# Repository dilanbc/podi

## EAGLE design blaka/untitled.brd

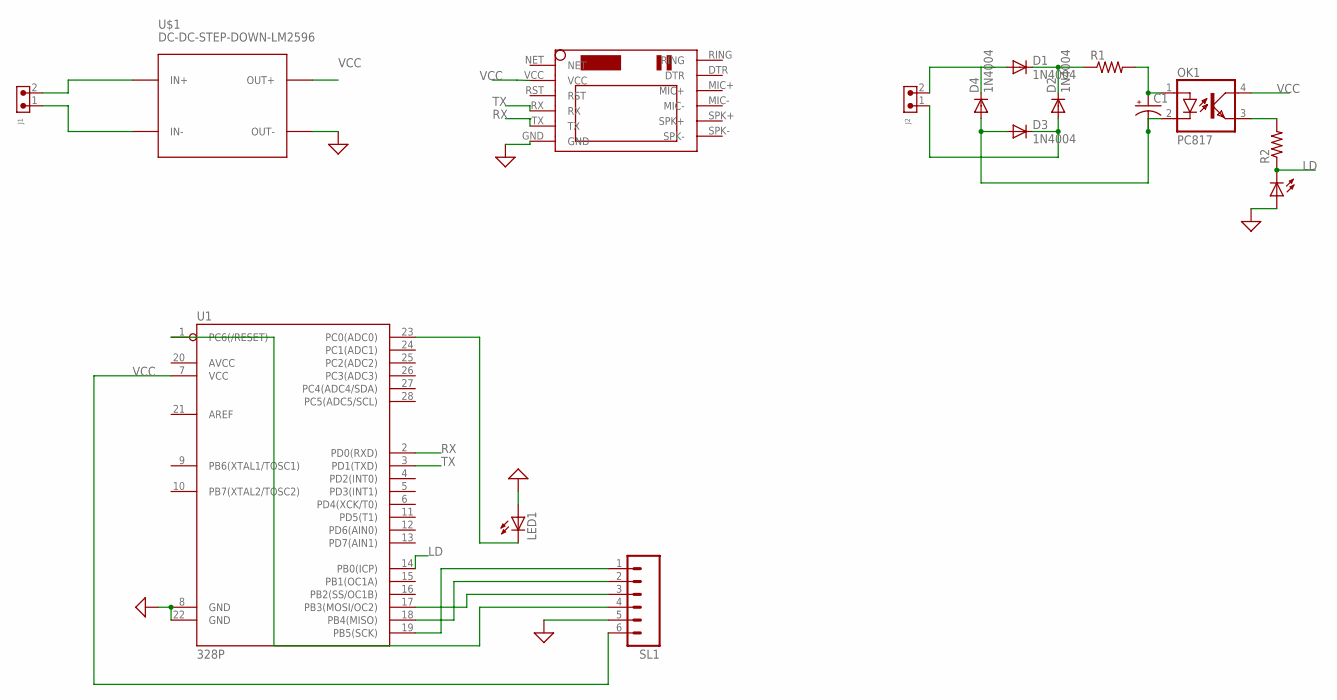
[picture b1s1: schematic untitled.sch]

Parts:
C1: CPOL-USE2.5-5; E2,5-5
D1, D2, D3, D4: 1N4004; DO41-10
J1, J2: 691305530002
LED1, LED2: LED5MM
OK1: PC817; DIL04
R1, R2: R-US_0207/10; 0207/10
SL1: M06; 06P
U1: 328P; DIP28
U$1: DC-DC-STEP-DOWN-LM2596
U$2: SIM800LMODULE

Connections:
GND: LED1.A, LED2.A, SL1.5, U1.8 (GND), U1.22 (GND), U$1.OUT-, U$2.GND
LD: LED2.K (C), OK1.3 (EMIT), R2.1, R2.2, U1.14 (PB0(ICP))
unnamed: J1.2, U$1.IN+
unnamed: J1.1, U$1.IN-
unnamed: D1.A, D4.C, J2.2
unnamed: SL1.1, U1.19 (PB5(SCK))
unnamed: SL1.2, U1.18 (PB4(MISO))
unnamed: SL1.3, U1.17 (PB3(MOSI/OC2))
unnamed: SL1.4, U1.1 (PC6(/RESET))
unnamed: LED1.K (C), U1.23 (PC0(ADC0))
unnamed: D1.C, D2.C, R1.1
unnamed: D2.A, D3.C, J2.1
unnamed: C1.-, D3.A, D4.A, OK1.2 (C)
unnamed: C1.+, OK1.1 (A), R1.2
RX: U1.2 (PD0(RXD)), U$2.TX
TX: U1.3 (PD1(TXD)), U$2.RX
VCC: OK1.4 (COL), SL1.6, U1.7 (VCC), U$1.OUT+, U$2.VCC

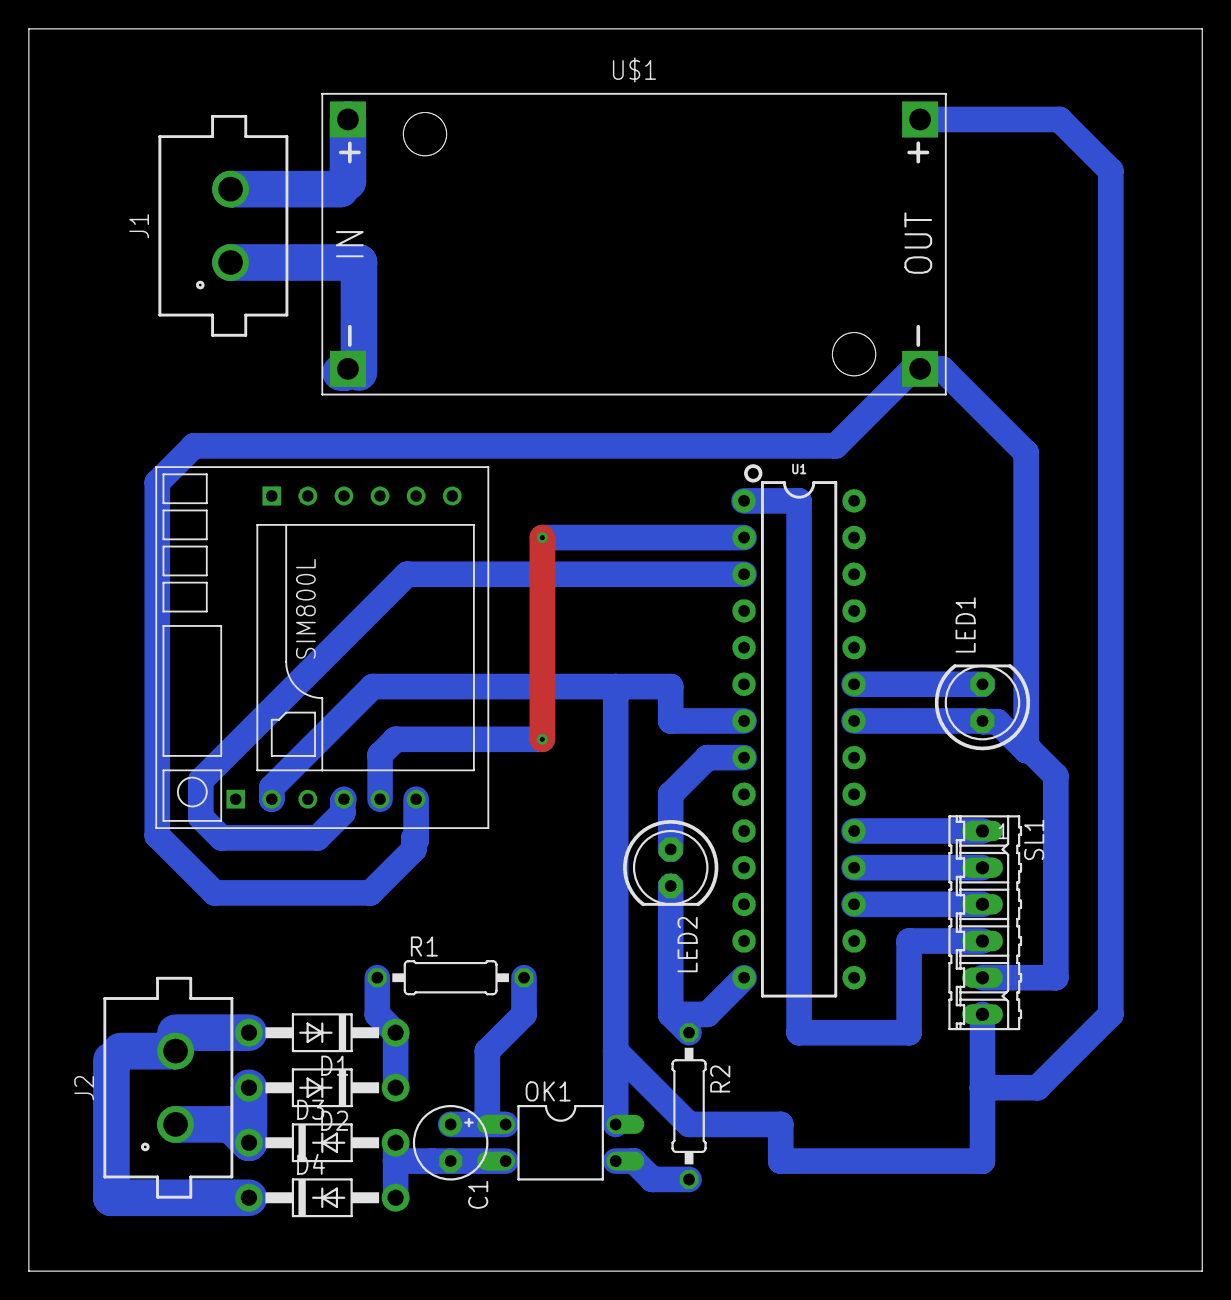
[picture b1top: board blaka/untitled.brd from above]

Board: 2 copper layers, 81.3 x 86.0 mm, 16 parts (0 on the bottom side), 17 nets.

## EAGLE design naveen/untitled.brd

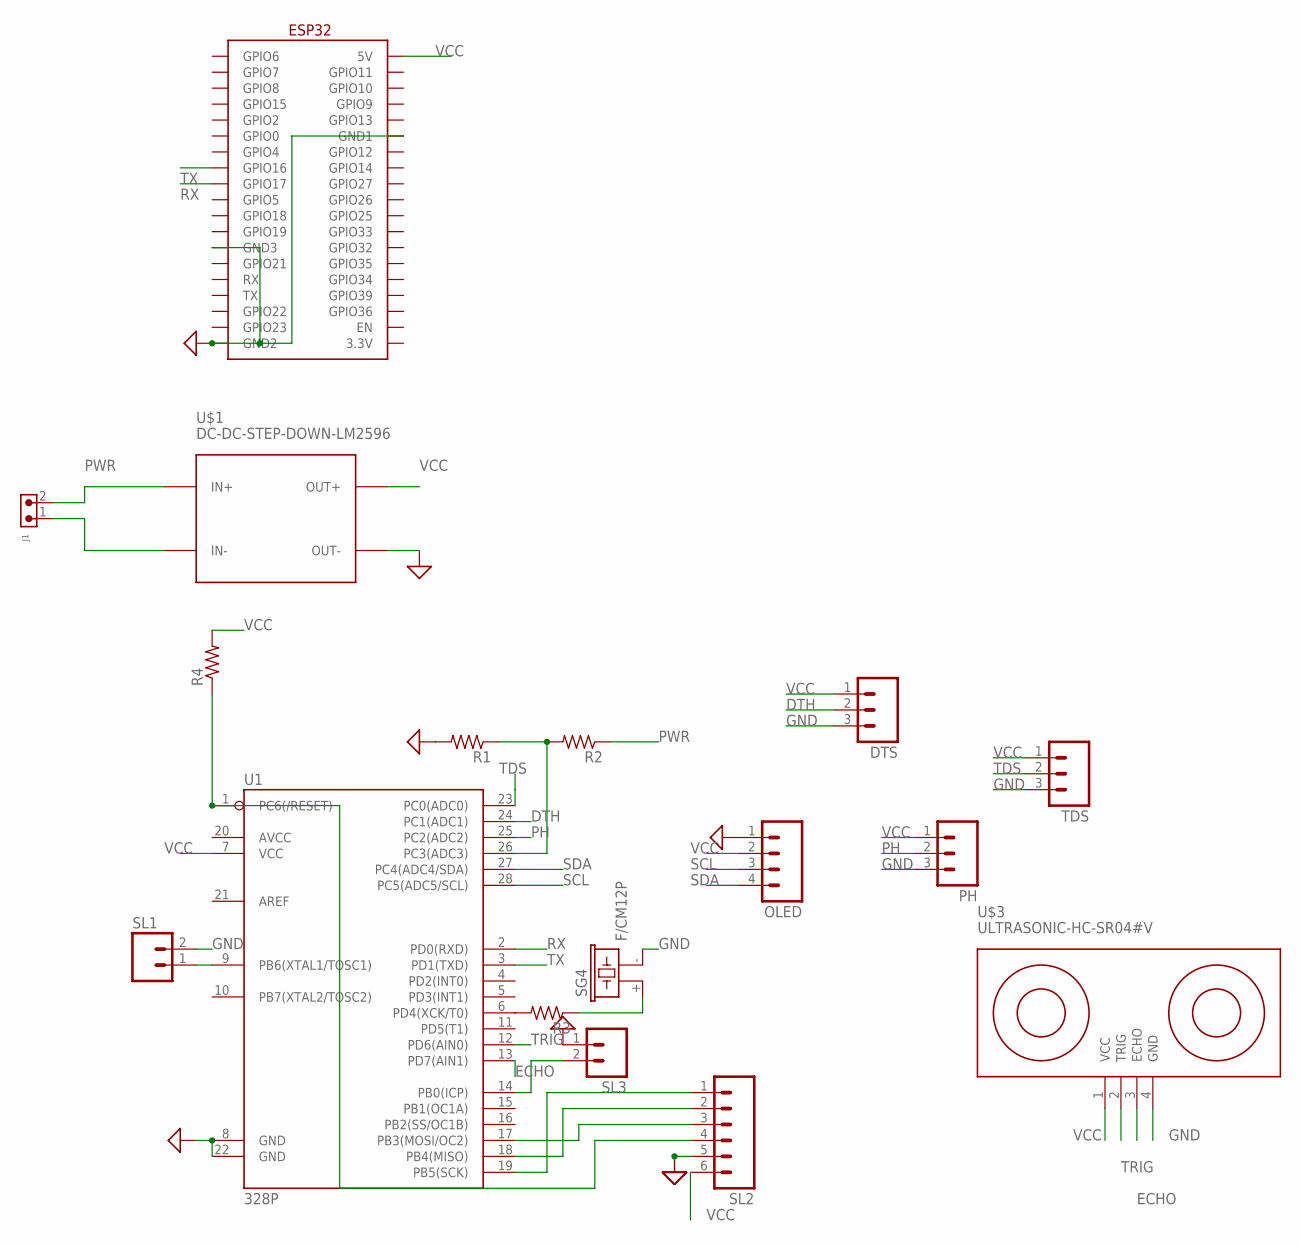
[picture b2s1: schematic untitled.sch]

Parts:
DTS: M03; 03P
J1: 691305530002
OLED: M04; 04P
PH: M03; 03P
R1, R2, R4: R-US_0207/10; 0207/10
R3: R-US_0204/2V; 0204V
SG4: F/CM12P
SL1, SL3: M02; 02P
SL2: M06; 06P
TDS: M03; 03P
U1: 328P; DIP28
U$1: DC-DC-STEP-DOWN-LM2596
U$2: ESP32
U$3: ULTRASONIC-HC-SR04#V

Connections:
DTH: DTS.2, U1.24 (PC1(ADC1))
ECHO: U1.13 (PD7(AIN1)), U$3.3 (ECHO)
GND: DTS.3, OLED.1, PH.3, R1.2, SG4.- (2), SL1.2, SL2.5, SL3.1, TDS.3, U1.8 (GND), U1.22 (GND), U$1.OUT-, U$2.GND1, U$2.GND2, U$2.GND3, U$3.4 (GND)
unnamed: R1.1, R2.2, U1.26 (PC3(ADC3))
unnamed: J1.1, U$1.IN-
unnamed: SL3.2, U1.14 (PB0(ICP))
unnamed: SL2.1, U1.19 (PB5(SCK))
unnamed: SL2.2, U1.18 (PB4(MISO))
unnamed: SL2.3, U1.17 (PB3(MOSI/OC2))
unnamed: R4.1, SL2.4, U1.1 (PC6(/RESET))
unnamed: SL1.1, U1.9 (PB6(XTAL1/TOSC1))
unnamed: R3.2, U1.6 (PD4(XCK/T0))
unnamed: R3.1, SG4.+ (1)
PH: PH.2, U1.25 (PC2(ADC2))
PWR: J1.2, R2.1, U$1.IN+
RX: U1.2 (PD0(RXD)), U$2.GPIO17
SCL: OLED.3, U1.28 (PC5(ADC5/SCL))
SDA: OLED.4, U1.27 (PC4(ADC4/SDA))
TDS: TDS.2, U1.23 (PC0(ADC0))
TRIG: U1.12 (PD6(AIN0)), U$3.2 (TRIG)
TX: U1.3 (PD1(TXD)), U$2.GPIO16
VCC: DTS.1, OLED.2, PH.1, R4.2, SL2.6, TDS.1, U1.7 (VCC), U$1.OUT+, U$2.5V, U$3.1 (VCC)

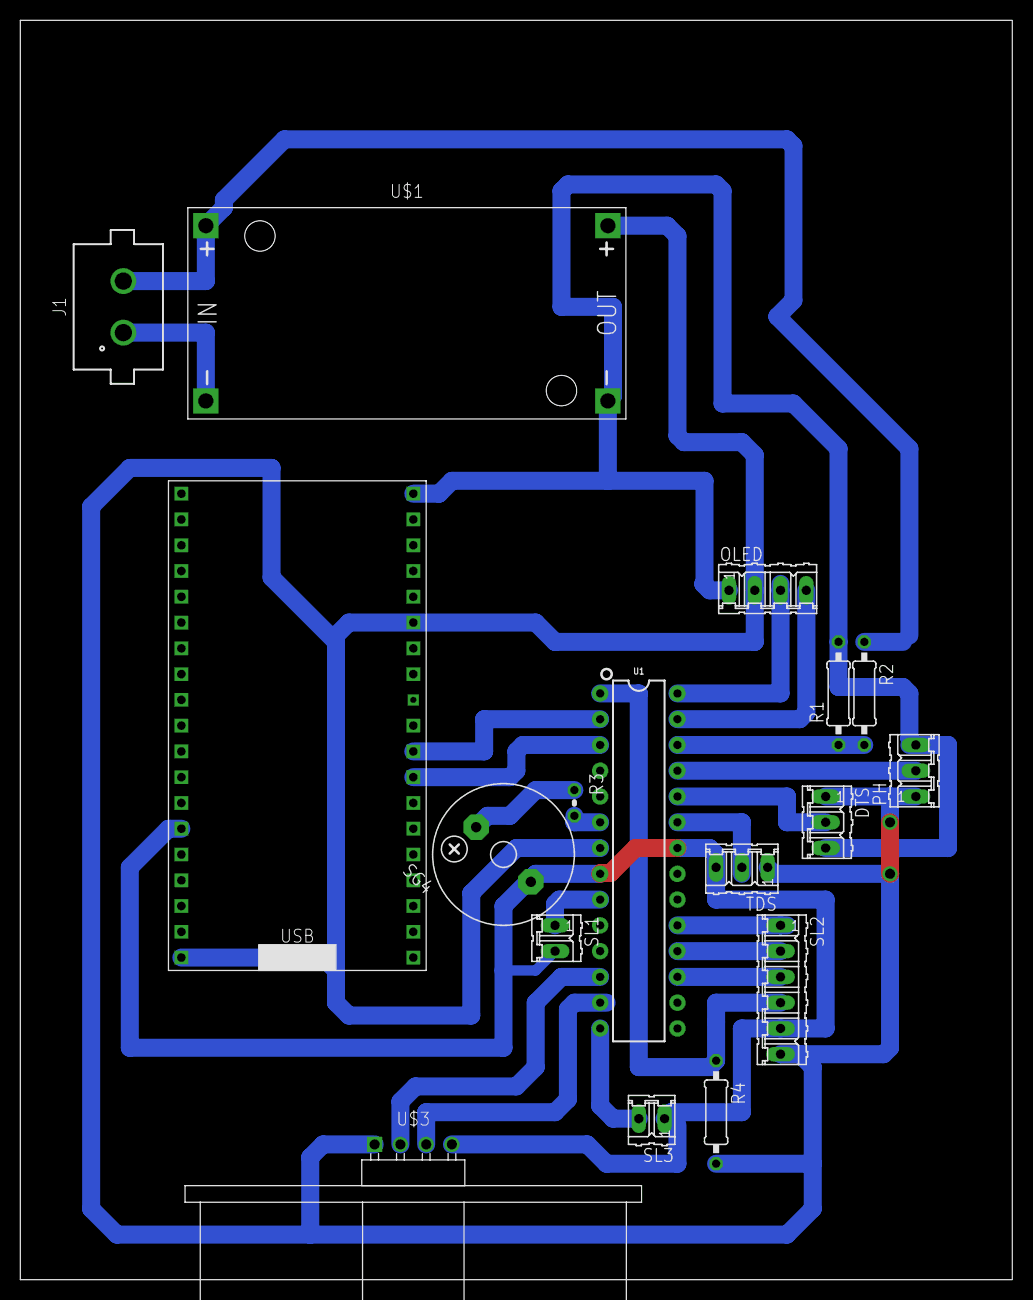
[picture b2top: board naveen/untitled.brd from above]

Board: 2 copper layers, 97.8 x 124.1 mm, 17 parts (0 on the bottom side), 22 nets.

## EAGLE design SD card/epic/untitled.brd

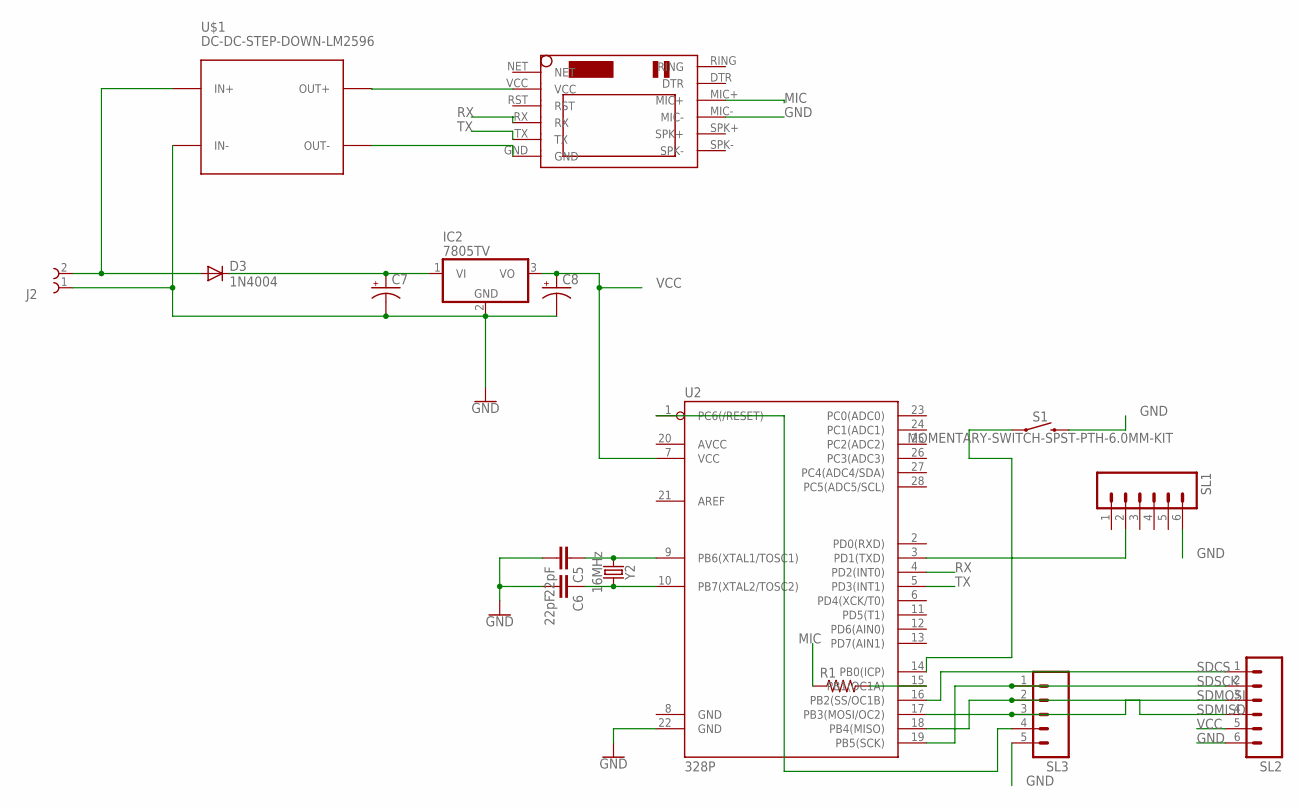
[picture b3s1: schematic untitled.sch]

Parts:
C5, C6: 22pF; CAP-PTH-2.54
C7: CAPACITOR-PE5-8.5; E5-8,5
C8: CAPACITOR-PE5-5; E5-5
D3: 1N4004; DO41-10
IC2: 7805TV; TO220V
J2: 691201520002
R1: R-US_0207/10; 0207/10
S1: MOMENTARY-SWITCH-SPST-PTH-6.0MM-KIT; TACTILE_SWITCH_PTH_6.0MM_KIT
SL1, SL2: M06; 06P
SL3: M05; 05P
U2: 328P; DIP28
U$1: DC-DC-STEP-DOWN-LM2596
U$2: SIM800LMODULE
Y2: 16MHz; HC49US

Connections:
GND: C5.2, C6.2, C7.-, C8.-, IC2.2 (GND), J2.1, S1.3 (2), SL1.6, SL2.6, SL3.5, U2.22 (GND), U$1.IN-, U$2.MIC-
MIC: R1.1, U$2.MIC+
unnamed: U$1.OUT+, U$2.VCC
unnamed: U$1.OUT-, U$2.GND
unnamed: R1.2, U2.15 (PB1(OC1A))
unnamed: S1.1, U2.14 (PB0(ICP))
unnamed: SL3.4, U2.1 (PC6(/RESET))
unnamed: C5.1, U2.9 (PB6(XTAL1/TOSC1)), Y2.1
unnamed: C6.1, U2.10 (PB7(XTAL2/TOSC2)), Y2.2
unnamed: D3.A, J2.2, U$1.IN+
unnamed: C7.+, D3.C, IC2.1 (VI)
RX: U2.4 (PD2(INT0)), U$2.RX
SDCS: SL2.1, U2.16 (PB2(SS/OC1B))
SDMISO: SL2.4, SL3.2, U2.18 (PB4(MISO))
SDMOSI: SL2.3, SL3.3, U2.17 (PB3(MOSI/OC2))
SDSCK: SL2.2, SL3.1, U2.19 (PB5(SCK))
TX: U2.5 (PD3(INT1)), U$2.TX
TX1: SL1.2, U2.3 (PD1(TXD))
VCC: C8.+, IC2.3 (VO), SL2.5, U2.7 (VCC)

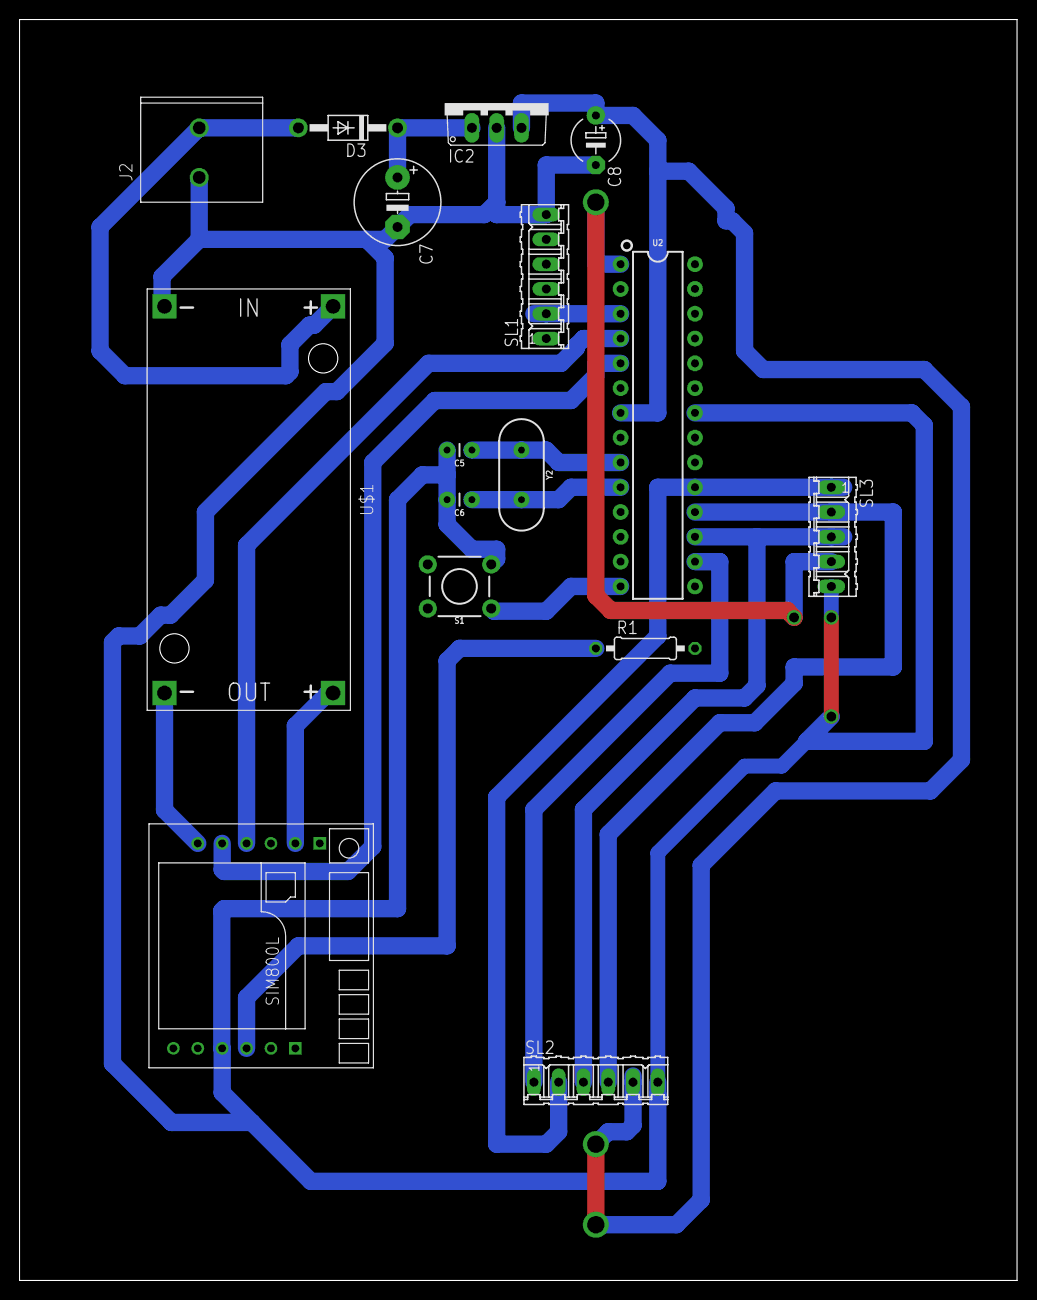
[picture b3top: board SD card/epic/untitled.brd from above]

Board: 2 copper layers, 102.2 x 129.2 mm, 16 parts (0 on the bottom side), 19 nets.

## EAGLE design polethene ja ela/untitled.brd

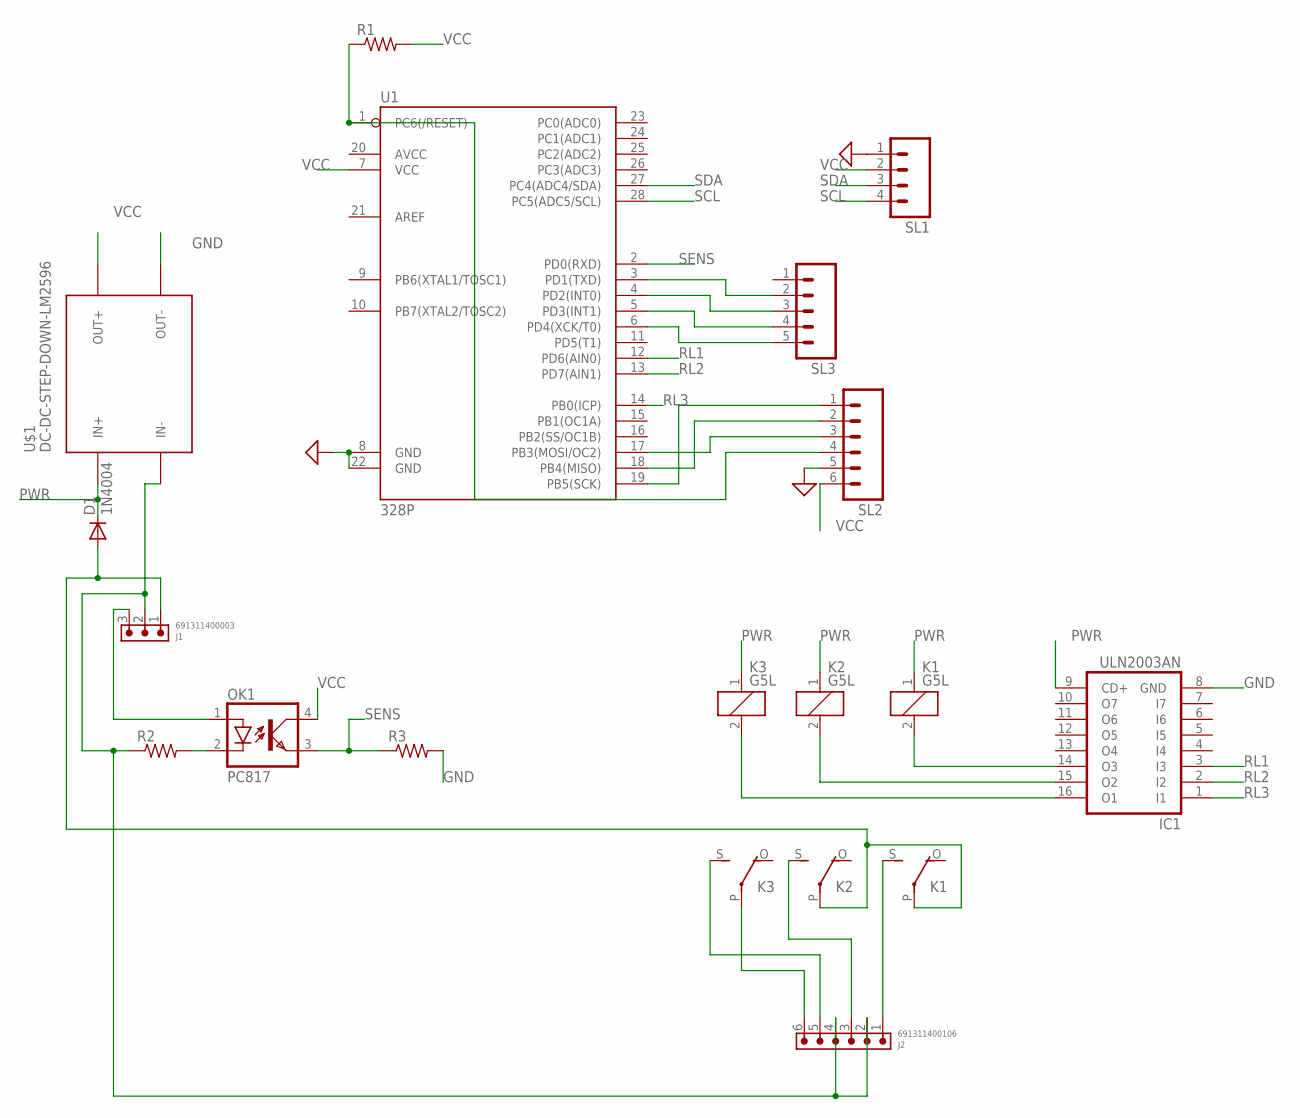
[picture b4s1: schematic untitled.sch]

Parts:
D1: 1N4004; DO41-10
IC1: ULN2003AN; DIL16
J1: 691311400003
J2: 691311400106
K1, K2, K3: G5L; G5LE
OK1: PC817; DIL04
R1, R2, R3: R-US_0207/7; 0207/7
SL1: M04; 04P
SL2: M06; 06P
SL3: M05; 05P
U1: 328P; DIP28
U$1: DC-DC-STEP-DOWN-LM2596

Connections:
GND: IC1.8 (GND), R3.2, SL1.1, SL2.5, U1.8 (GND), U1.22 (GND), U$1.OUT-
unnamed: J2.1, K1.S
unnamed: D1.A, J1.1, K1.P, K2.P
unnamed: J1.3, OK1.1 (A)
unnamed: SL2.1, U1.19 (PB5(SCK))
unnamed: SL2.2, U1.18 (PB4(MISO))
unnamed: SL2.3, U1.17 (PB3(MOSI/OC2))
unnamed: R1.1, SL2.4, U1.1 (PC6(/RESET))
unnamed: OK1.2 (C), R2.2
unnamed: J2.3, K2.S
unnamed: SL3.2, U1.3 (PD1(TXD))
unnamed: J2.5, K3.S
unnamed: J2.6, K3.P
unnamed: IC1.14 (O3), K1.2
unnamed: IC1.15 (O2), K2.2
unnamed: IC1.16 (O1), K3.2
unnamed: J1.2, J2.2, J2.4, R2.1, U$1.IN-
unnamed: SL3.3, U1.4 (PD2(INT0))
unnamed: SL3.4, U1.5 (PD3(INT1))
unnamed: SL3.5, U1.6 (PD4(XCK/T0))
PWR: D1.C, IC1.9 (CD+), K1.1, K2.1, K3.1, U$1.IN+
RL1: IC1.3 (I3), U1.12 (PD6(AIN0))
RL2: IC1.2 (I2), U1.13 (PD7(AIN1))
RL3: IC1.1 (I1), U1.14 (PB0(ICP))
SCL: SL1.4, U1.28 (PC5(ADC5/SCL))
SDA: SL1.3, U1.27 (PC4(ADC4/SDA))
SENS: OK1.3 (EMIT), R3.1, U1.2 (PD0(RXD))
VCC: OK1.4 (COL), R1.2, SL1.2, SL2.6, U1.7 (VCC), U$1.OUT+

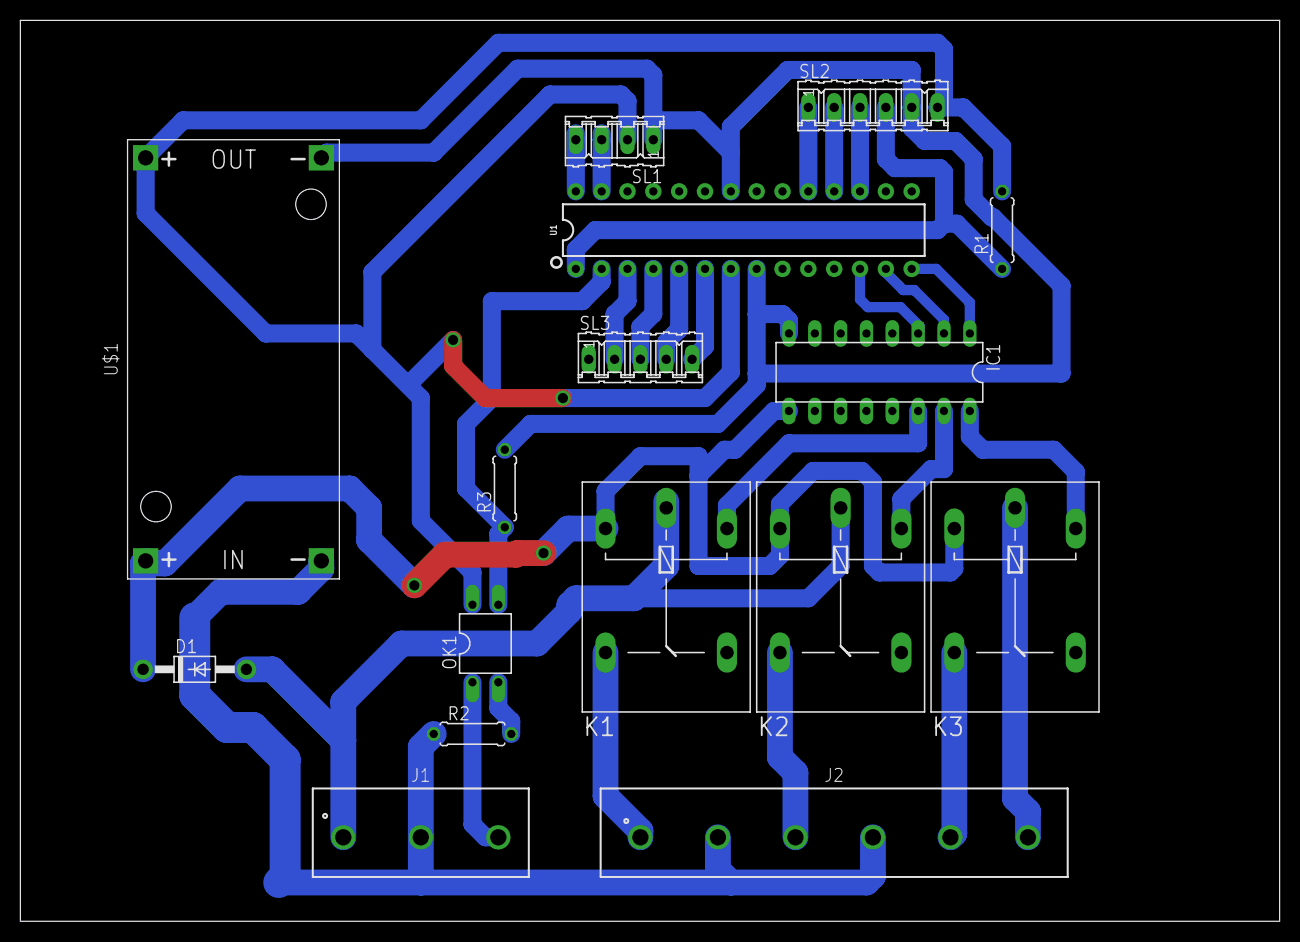
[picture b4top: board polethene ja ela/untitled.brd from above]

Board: 2 copper layers, 123.8 x 88.6 mm, 16 parts (0 on the bottom side), 28 nets.

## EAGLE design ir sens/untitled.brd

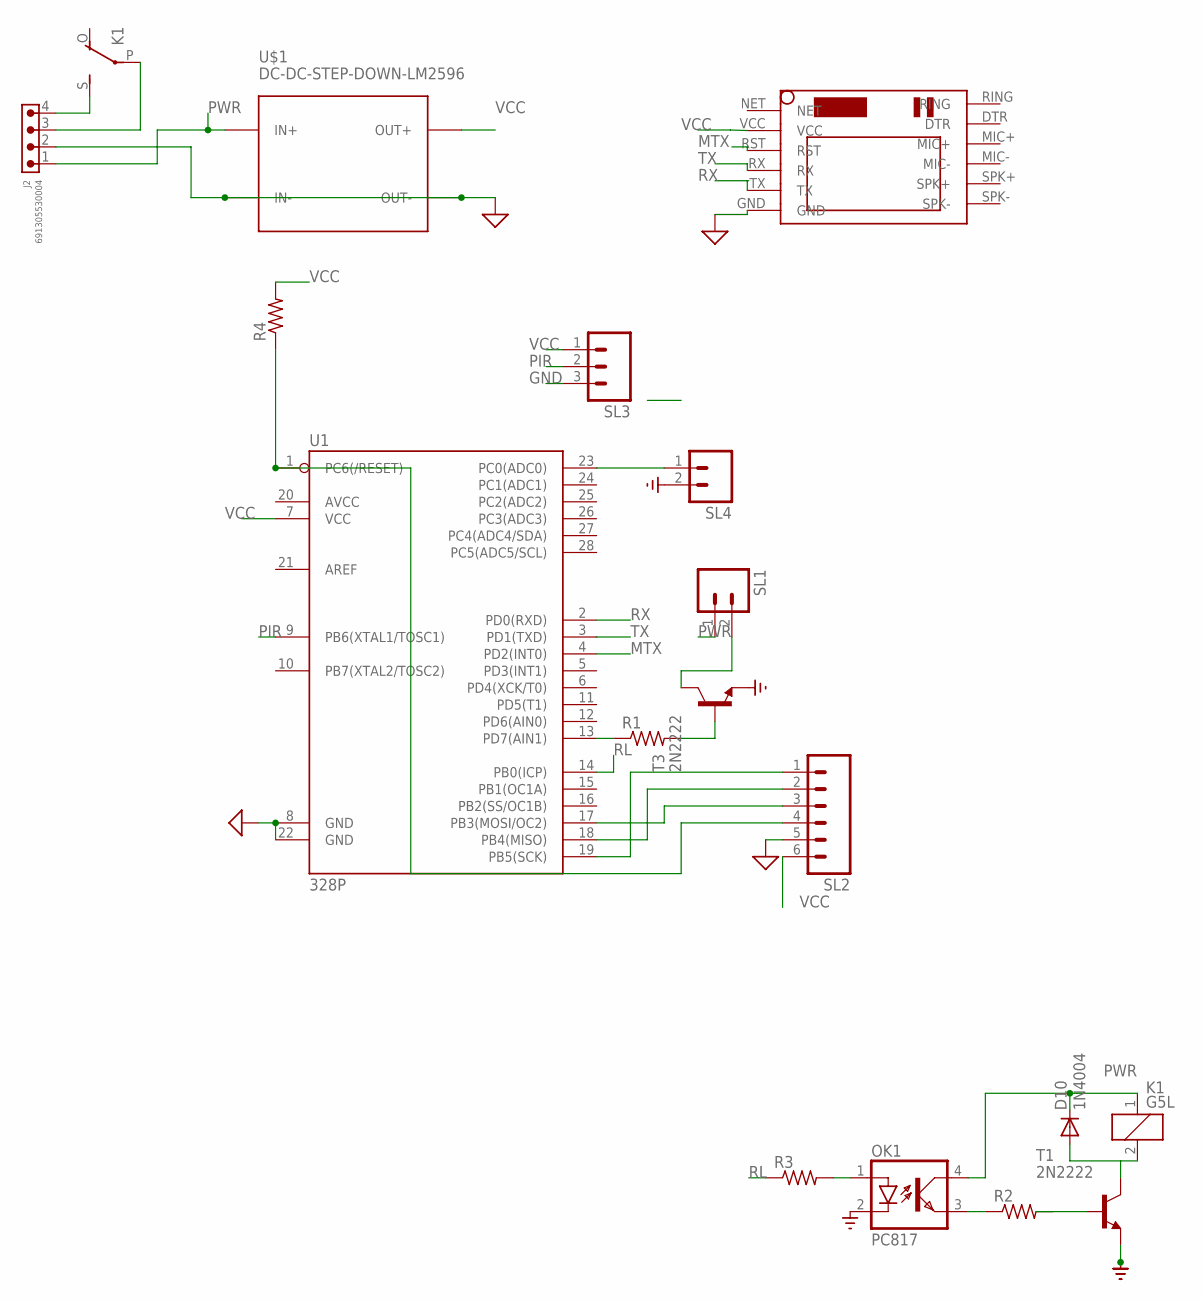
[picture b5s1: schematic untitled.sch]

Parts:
D10: 1N4004; DO41-10
J2: 691305530004
K1: G5L; G5LE
OK1: PC817; DIL04
R1, R2: R-US_0207/10; 0207/10
R3, R4: R-US_0207/15; 0207/15
SL1, SL4: M02; 02P
SL2: M06; 06P
SL3: M03; 03P
T1, T3: 2N2222; TO92-EBC-OVAL
U1: 328P; DIP28
U$1: DC-DC-STEP-DOWN-LM2596
U$2: SIM800LMODULE

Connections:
GND: J2.2, OK1.2 (C), SL2.5, SL3.3, SL4.2, T1.E, T3.E, U1.8 (GND), U1.22 (GND), U$1.IN-, U$1.OUT-, U$2.GND
MTX: U1.4 (PD2(INT0)), U$2.RST
unnamed: OK1.1 (A), R3.2
unnamed: SL1.2, T3.C
unnamed: J2.4, K1.S
unnamed: SL2.1, U1.19 (PB5(SCK))
unnamed: SL2.2, U1.18 (PB4(MISO))
unnamed: SL2.3, U1.17 (PB3(MOSI/OC2))
unnamed: R1.1, U1.13 (PD7(AIN1))
unnamed: J2.3, K1.P
unnamed: D10.A, K1.2, T1.C
unnamed: R1.2, T3.B
unnamed: SL4.1, U1.23 (PC0(ADC0))
unnamed: R2.2, T1.B
unnamed: OK1.3 (EMIT), R2.1
unnamed: R4.1, SL2.4, U1.1 (PC6(/RESET))
PIR: SL3.2, U1.9 (PB6(XTAL1/TOSC1))
PWR: D10.C, J2.1, K1.1, OK1.4 (COL), SL1.1, U$1.IN+
RL: R3.1, U1.14 (PB0(ICP))
RX: U1.2 (PD0(RXD)), U$2.TX
TX: U1.3 (PD1(TXD)), U$2.RX
VCC: R4.2, SL2.6, SL3.1, U1.7 (VCC), U$1.OUT+, U$2.VCC

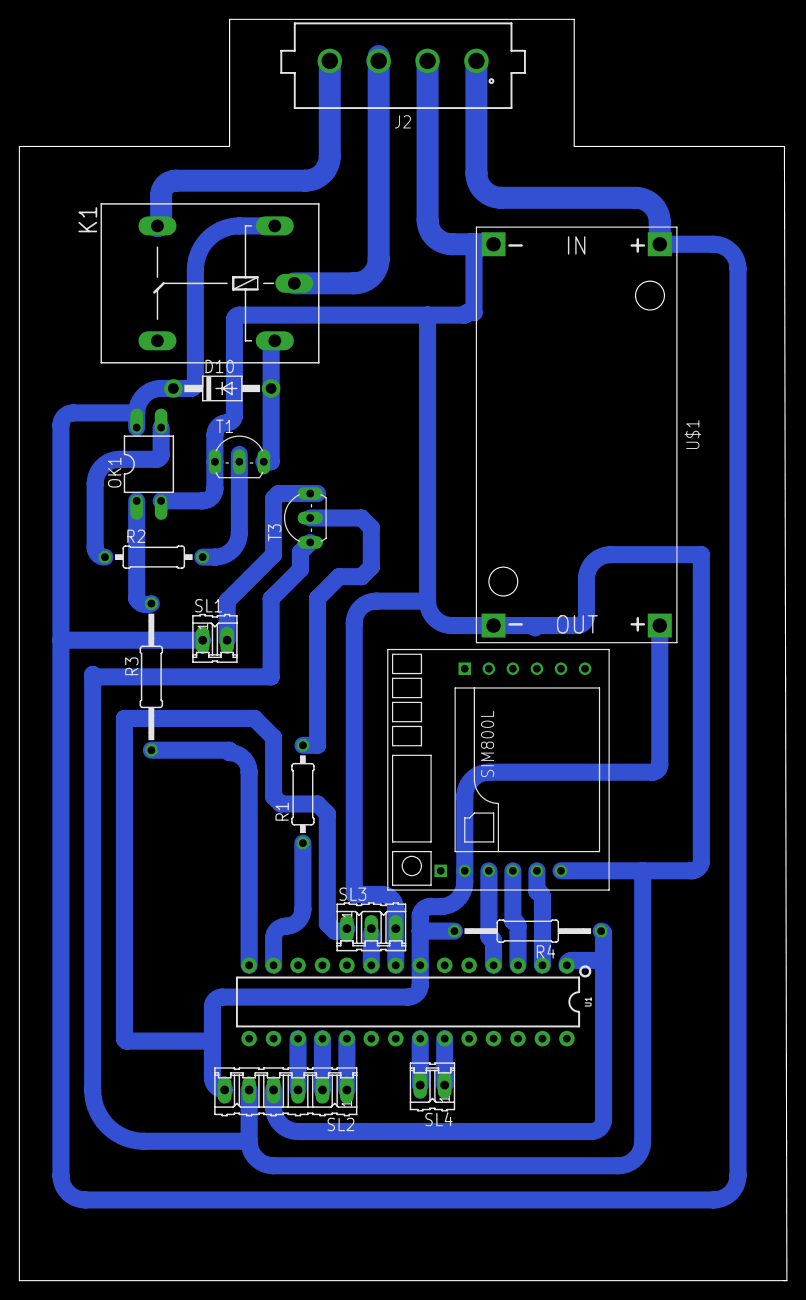
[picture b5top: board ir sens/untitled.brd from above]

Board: 2 copper layers, 79.8 x 131.1 mm, 17 parts (0 on the bottom side), 22 nets.

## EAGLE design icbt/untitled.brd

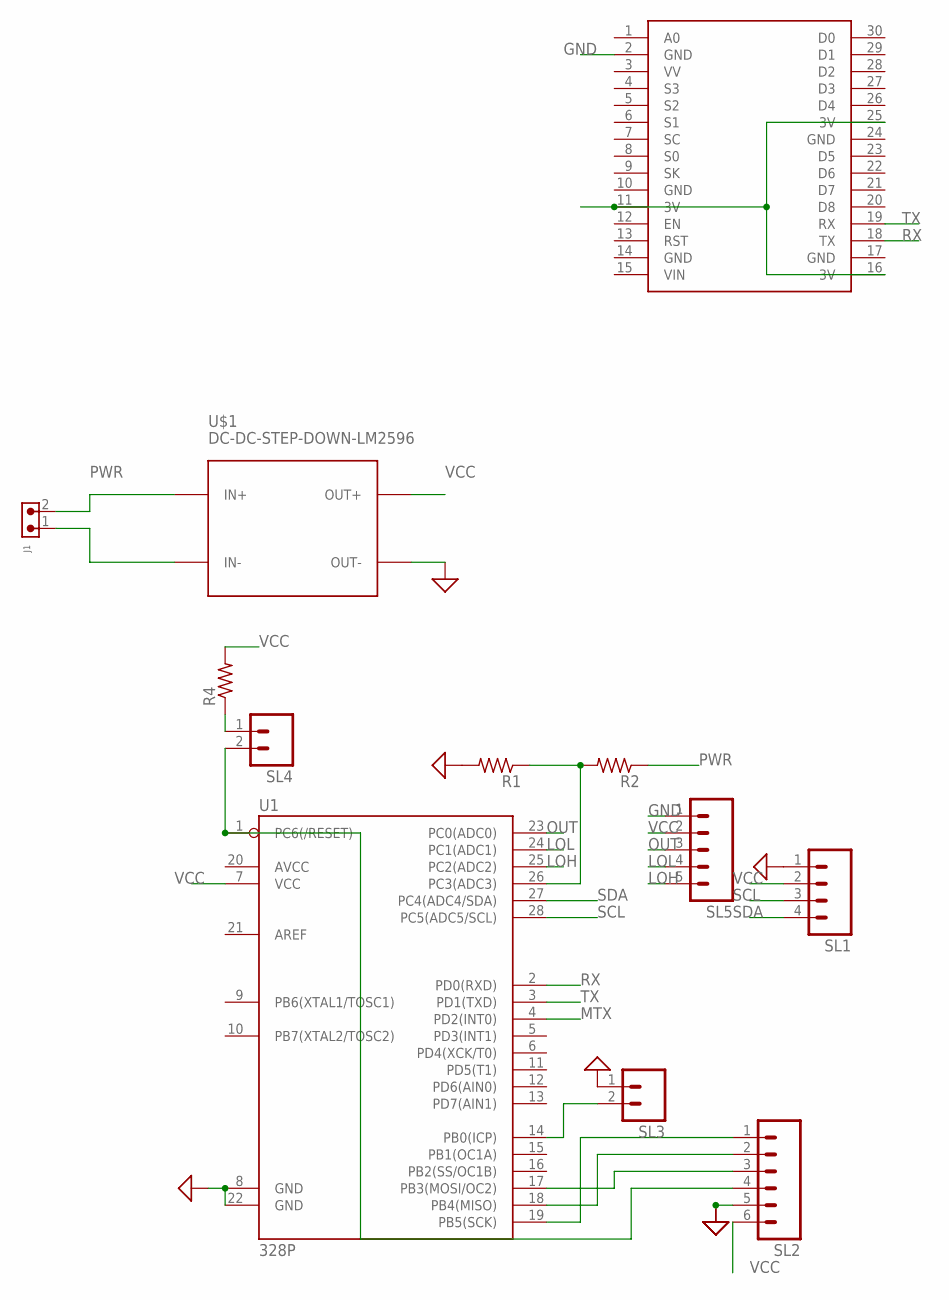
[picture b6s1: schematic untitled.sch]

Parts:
J1: 691305530002
R1, R2, R4: R-US_0207/10; 0207/10
SL1: M04; 04P
SL2: M06; 06P
SL3, SL4: M02; 02P
SL5: M05; 05P
U1: 328P; DIP28
U$1: DC-DC-STEP-DOWN-LM2596
U$3: NODEMCU

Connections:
GND: R1.2, SL1.1, SL2.5, SL3.1, SL5.1, U1.8 (GND), U1.22 (GND), U$1.OUT-, U$3.2 (GND), U$3.10 (GND), U$3.14 (GND), U$3.17 (GND), U$3.24 (GND)
LOH: SL5.5, U1.25 (PC2(ADC2))
LOL: SL5.4, U1.24 (PC1(ADC1))
MTX: U1.4 (PD2(INT0))
unnamed: R1.1, R2.2, U1.26 (PC3(ADC3))
unnamed: J1.1, U$1.IN-
unnamed: SL3.2, U1.14 (PB0(ICP))
unnamed: SL2.1, U1.19 (PB5(SCK))
unnamed: SL2.2, U1.18 (PB4(MISO))
unnamed: SL2.3, U1.17 (PB3(MOSI/OC2))
unnamed: SL2.4, SL4.2, U1.1 (PC6(/RESET))
unnamed: R4.1, SL4.1
OUT: SL5.3, U1.23 (PC0(ADC0))
PWR: J1.2, R2.1, U$1.IN+
RX: U1.2 (PD0(RXD)), U$3.18 (TX)
SCL: SL1.3, U1.28 (PC5(ADC5/SCL))
SDA: SL1.4, U1.27 (PC4(ADC4/SDA))
TX: U1.3 (PD1(TXD)), U$3.19 (RX)
VCC: R4.2, SL1.2, SL2.6, SL5.2, U1.7 (VCC), U$1.OUT+, U$3.11 (3V), U$3.16 (3V), U$3.25 (3V)

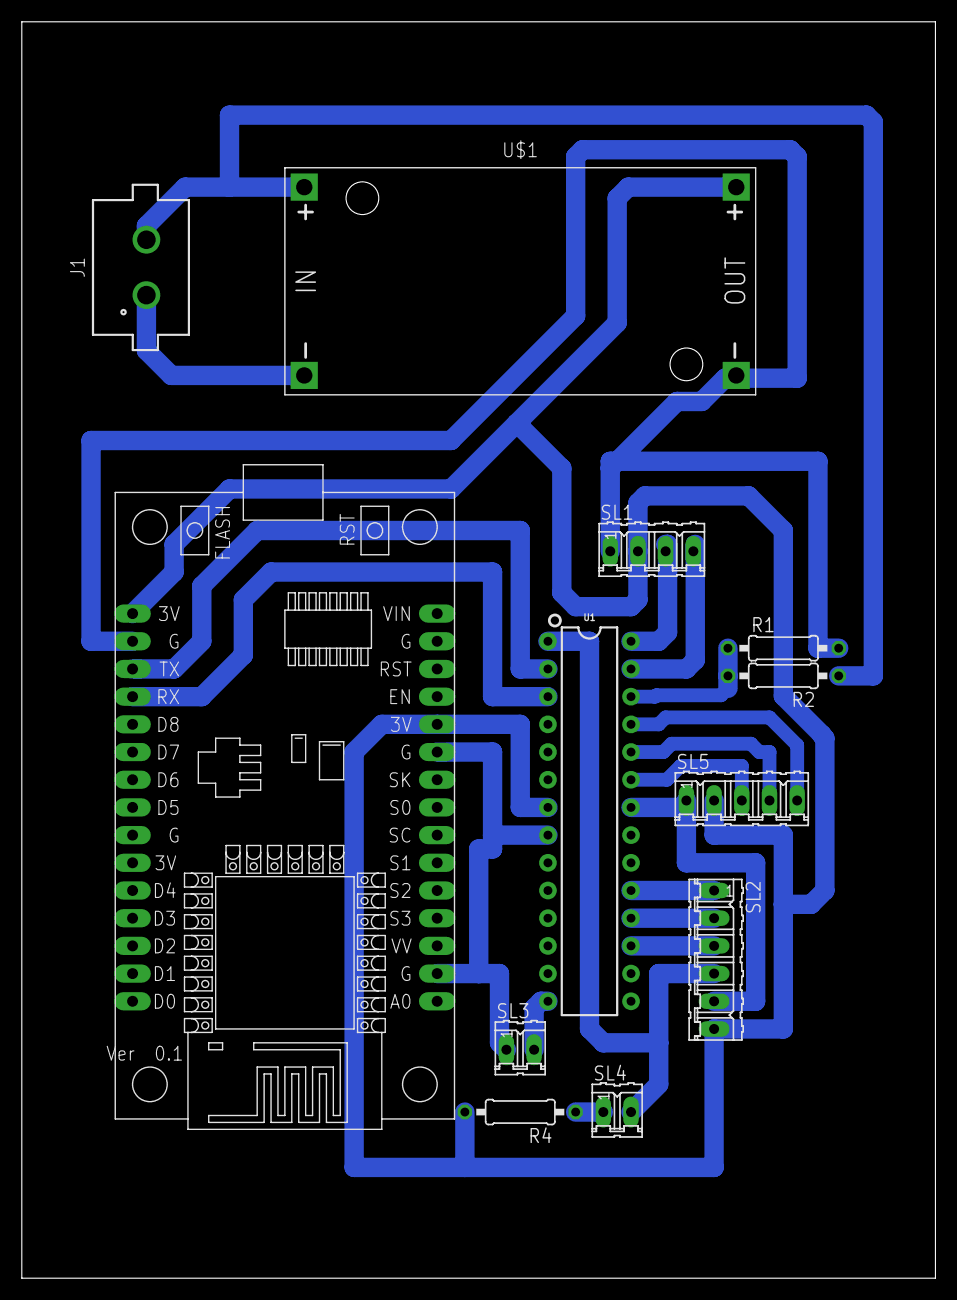
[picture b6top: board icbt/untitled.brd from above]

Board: 2 copper layers, 83.8 x 115.2 mm, 12 parts (0 on the bottom side), 18 nets.

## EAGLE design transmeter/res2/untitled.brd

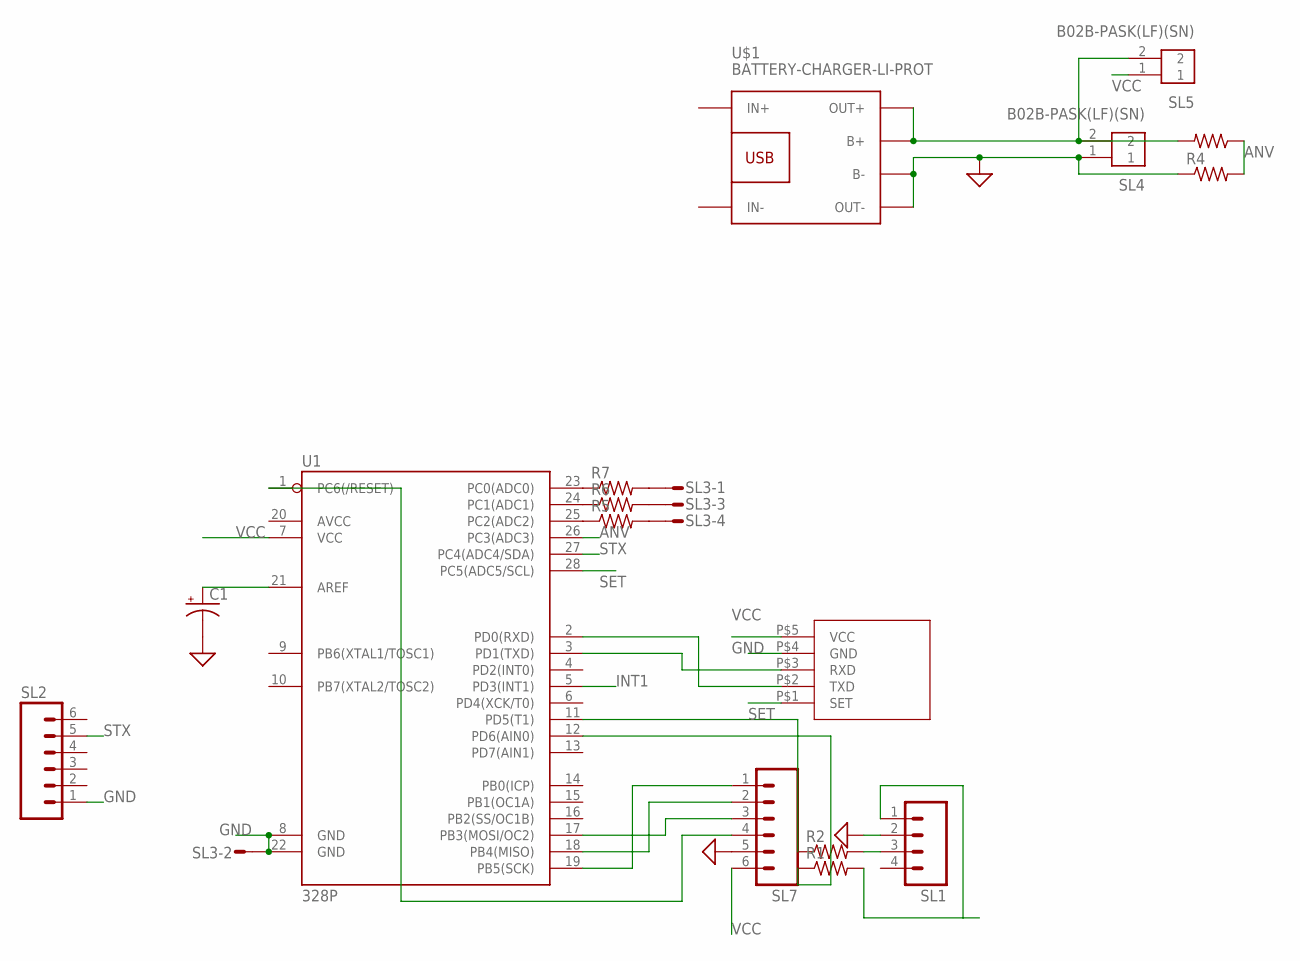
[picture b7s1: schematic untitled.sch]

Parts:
C1: CAPACITOR-PE2.5-5; E2,5-5
R1, R2: R-US_0309/10; 0309/10
R4, R8: R-US_0207/7; 0207/7
R5, R6: R-US_0204/2V; 0204V
R7: R-US_0207/5V; 0207/5V
SL1: M04; 04P
SL2, SL7: M06; 06P
SL3: M04S; 04P
SL4, SL5: B02B-PASK(LF)(SN)
U1: 328P; DIP28
U$1: BATTERY-CHARGER-LI-PROT
U$3: HC12

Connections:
ANV: R4.2, R8.1, U1.26 (PC3(ADC3))
GND: C1.-, R4.1, SL1.2, SL2.1, SL3.2, SL4.1, SL7.5, U1.8 (GND), U1.22 (GND), U$1.B-, U$1.OUT-, U$3.P$4 (GND)
INT1: U1.5 (PD3(INT1))
unnamed: C1.+, U1.21 (AREF)
unnamed: R1.2, SL1.1
unnamed: SL7.1, U1.19 (PB5(SCK))
unnamed: SL7.2, U1.18 (PB4(MISO))
unnamed: SL7.3, U1.17 (PB3(MOSI/OC2))
unnamed: SL7.4, U1.1 (PC6(/RESET))
unnamed: R2.2, SL1.3
unnamed: R2.1, U1.11 (PD5(T1))
unnamed: R1.1, U1.12 (PD6(AIN0))
unnamed: U1.2 (PD0(RXD)), U$3.P$2 (TXD)
unnamed: U1.3 (PD1(TXD)), U$3.P$3 (RXD)
unnamed: R5.1, U1.25 (PC2(ADC2))
unnamed: R5.2, SL3.4
unnamed: R6.1, U1.24 (PC1(ADC1))
unnamed: R6.2, SL3.3
unnamed: R7.1, U1.23 (PC0(ADC0))
unnamed: R7.2, SL3.1
unnamed: R8.2, SL4.2, SL5.2, U$1.B+, U$1.OUT+
SET: U1.28 (PC5(ADC5/SCL)), U$3.P$1 (SET)
STX: SL2.5, U1.27 (PC4(ADC4/SDA))
VCC: SL5.1, SL7.6, U1.7 (VCC), U$3.P$5 (VCC)

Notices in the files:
parts and their libraries:
Wurth_Connectors_WR-TBL Pluggable Connec: Copyright: Würth Elektronik
SparkFun-Boards: Licensing: Creative Commons ShareAlike 4.0 International - https://creativecommons.org/licenses/by-sa/4.0
